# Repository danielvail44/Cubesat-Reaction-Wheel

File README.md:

# Cubesat-Reaction-Wheel
Low Cost Cubesat Reaction Wheel

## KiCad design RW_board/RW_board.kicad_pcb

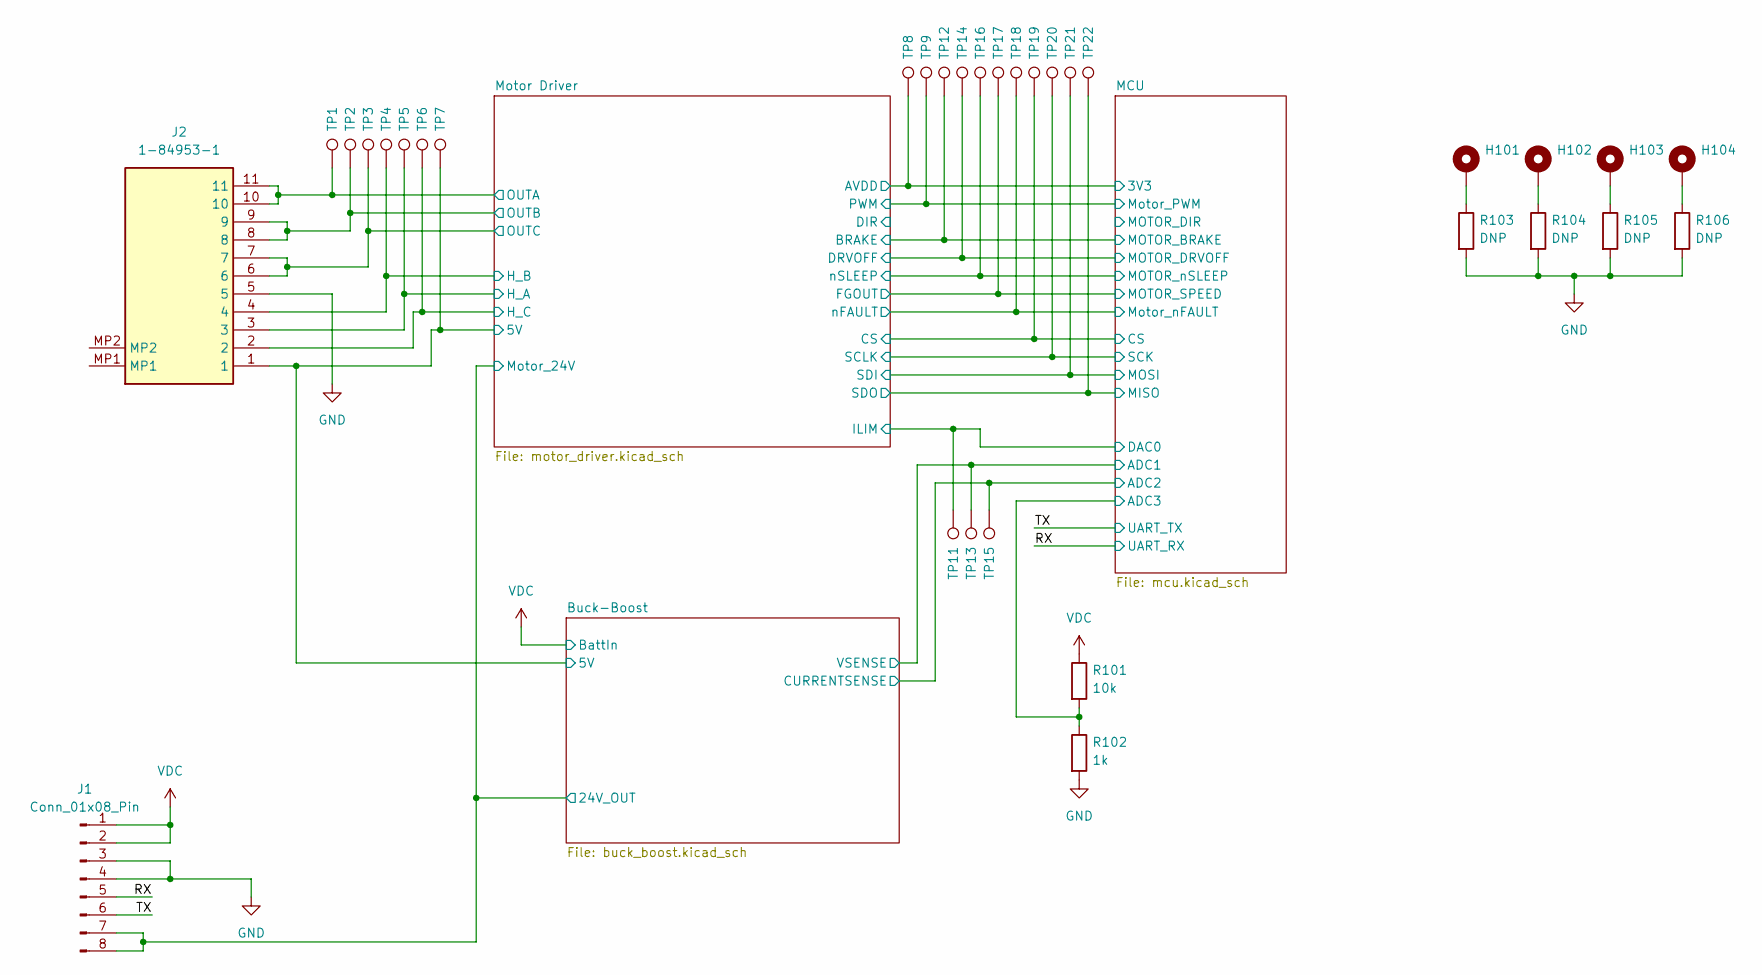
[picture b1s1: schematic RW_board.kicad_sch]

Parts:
H101, H102, H103, H104: MountingHole_Pad; MountingHole_3.4mm_Pad
J1: Conn_01x08_Pin; Molex_PicoBlade_53048-0810_1x08_P1.25mm_Horizontal; Mouser Part Number 538-53048-0810
J2: 1-84953-1; 1849531; Mouser Part Number 571-1-84953-1
R101: 10k; R_0402_1005Metric; Mouser Part Number 710-560112110020
R102: 1k; R_0402_1005Metric; Mouser Part Number 710-560112110012
R103, R104, R105, R106: DNP; R_0402_1005Metric
TP1, TP2, TP3, TP4, TP5, TP6, TP7, TP8, TP9, TP11, TP12, TP13, TP14, TP15, TP16, TP17, TP18, TP19, TP20, TP21, TP22: TestPoint; TestPoint_Pad_1.0x1.0mm

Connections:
+3.3V: TP8.1; also elsewhere on the board
/Buck-Boost/24V_OUT: J1.7, J1.8; also elsewhere on the board
/Buck-Boost/CURRENTSENSE: TP15.1; also elsewhere on the board
/Buck-Boost/VSENSE: TP13.1; also elsewhere on the board
/MCU/ADC3: R101.2, R102.1; also elsewhere on the board
/MCU/CS: TP19.1; also elsewhere on the board
/MCU/DAC0: TP11.1; also elsewhere on the board
/MCU/MISO: TP22.1; also elsewhere on the board
/MCU/MOSI: TP21.1; also elsewhere on the board
/MCU/MOTOR_BRAKE: TP12.1; also elsewhere on the board
/MCU/MOTOR_DRVOFF: TP14.1; also elsewhere on the board
/MCU/MOTOR_SPEED: TP17.1; also elsewhere on the board
/MCU/MOTOR_nSLEEP: TP16.1; also elsewhere on the board
/MCU/Motor_PWM: TP9.1; also elsewhere on the board
/MCU/Motor_nFAULT: TP18.1; also elsewhere on the board
/MCU/SCK: TP20.1; also elsewhere on the board
/Motor Driver/FB_BK: J2.1, TP7.1; also elsewhere on the board
/Motor Driver/H_A: J2.3, TP5.1; also elsewhere on the board
/Motor Driver/H_B: J2.4, TP4.1; also elsewhere on the board
/Motor Driver/H_C: J2.2, TP6.1; also elsewhere on the board
/Motor Driver/OUTA: J2.10, J2.11, TP1.1; also elsewhere on the board
/Motor Driver/OUTB: J2.8, J2.9, TP2.1; also elsewhere on the board
/Motor Driver/OUTC: J2.6, J2.7, TP3.1; also elsewhere on the board
/RX: J1.5; also elsewhere on the board
/TX: J1.6; also elsewhere on the board
GND: J1.3, J1.4, J2.5, R102.2, R103.2, R104.2, R105.2, R106.2; also elsewhere on the board
unnamed: H101.1, R103.1
unnamed: H102.1, R104.1
unnamed: H103.1, R105.1
unnamed: H104.1, R106.1
VDC: J1.1, J1.2, R101.1; also elsewhere on the board

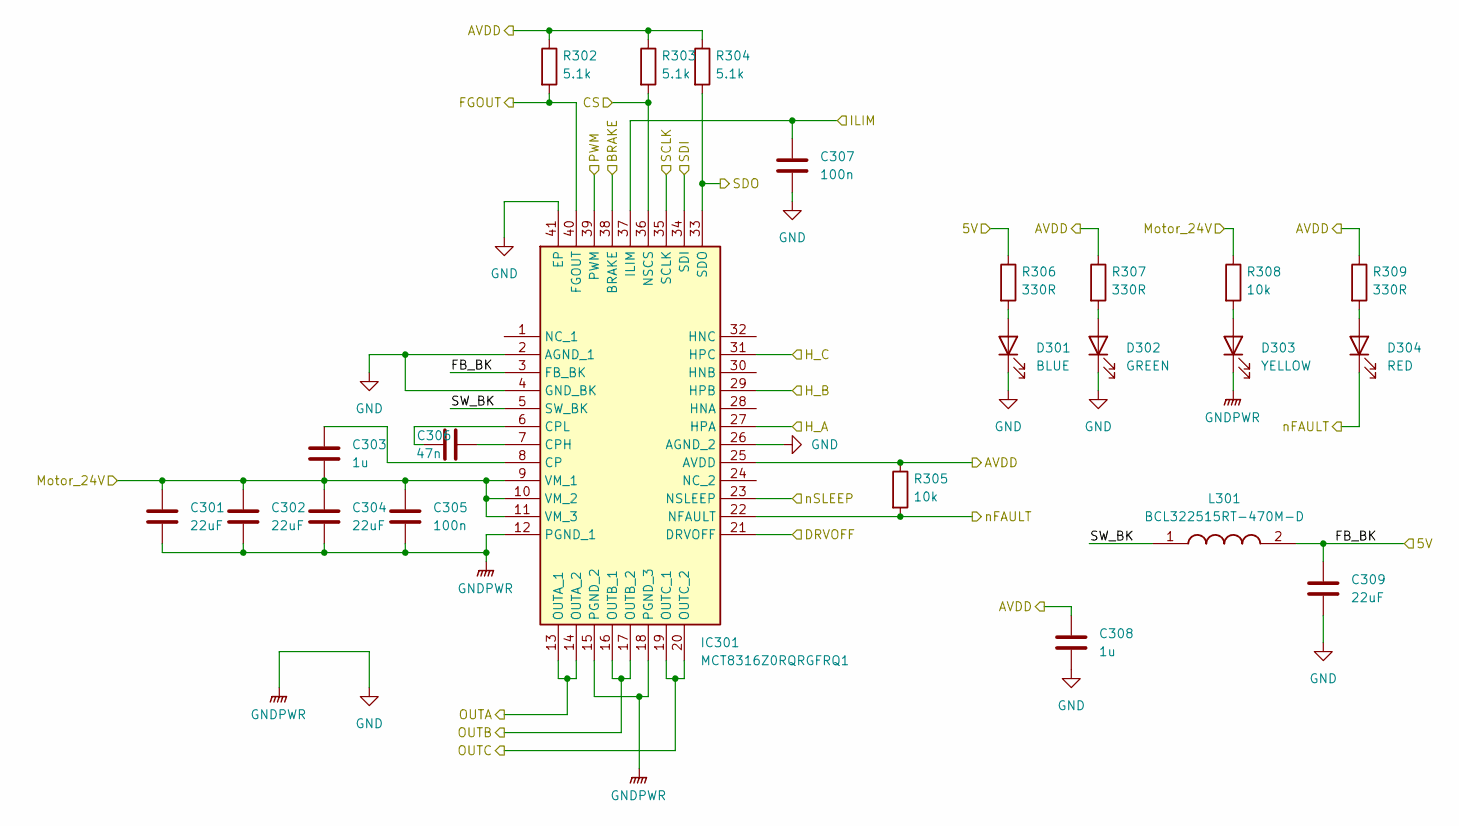
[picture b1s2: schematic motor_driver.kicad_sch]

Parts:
C301, C302, C304, C309: 22uF; C_0805_2012Metric; Voltage rating 35V; Mouser Part Number 810-C2012X5R1V226MAC
C303, C308: 1u; C_0402_1005Metric; Voltage rating 35V; Mouser Part Number 81-GRM155R6YA105KE1J
C305, C307: 100n; C_0402_1005Metric; Voltage rating 35V; Mouser Part Number 81-GRM155R61H104KE9J
C306: 47n; C_0402_1005Metric; Voltage rating 35V; Mouser Part Number 81-GRM155R61H473KE9D
D301: BLUE; LED_0603_1608Metric; Mouser Part Number 720-P4112P1R2363X4X5
D302: GREEN; LED_0603_1608Metric; Mouser Part Number 720-P4112S2U1252X4X5
D303: YELLOW; LED_0603_1608Metric; Mouser Part Number 720-P412Q2T136A8J802
D304: RED; LED_0603_1608Metric; Mouser Part Number 720-P412P1R258A8J802
IC301: MCT8316Z0RQRGFRQ1; QFN50P500X700X100-41N-D; Mouser Part Number 595-CT8316Z0RQRGFRQ1
L301: BCL322515RT-470M-D; INDPM3225X150N; Mouser Part Number 810-BCL322515RT470MD
R302, R303, R304: 5.1k; R_0402_1005Metric; Mouser Part Number 652-CR0402FX-5101GLF
R305, R308: 10k; R_0402_1005Metric; Mouser Part Number 710-560112110020
R306, R307, R309: 330R; R_0402_1005Metric; Mouser Part Number 710-560112110231

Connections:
+3.3V: C308.1, IC301.25 (AVDD), R302.1, R303.1, R304.1, R305.1, R307.1, R309.1; also elsewhere on the board
/Buck-Boost/24V_OUT: C301.1, C302.1, C303.2, C304.1, C305.1, IC301.9 (VM_1), IC301.10 (VM_2), IC301.11 (VM_3), R308.1; also elsewhere on the board
/MCU/CS: IC301.36 (NSCS), R303.2; also elsewhere on the board
/MCU/DAC0: C307.1, IC301.37 (ILIM); also elsewhere on the board
/MCU/MISO: IC301.33 (SDO), R304.2; also elsewhere on the board
/MCU/MOSI: IC301.34 (SDI); also elsewhere on the board
/MCU/MOTOR_BRAKE: IC301.38 (BRAKE); also elsewhere on the board
/MCU/MOTOR_DRVOFF: IC301.21 (DRVOFF); also elsewhere on the board
/MCU/MOTOR_SPEED: IC301.40 (FGOUT), R302.2; also elsewhere on the board
/MCU/MOTOR_nSLEEP: IC301.23 (NSLEEP); also elsewhere on the board
/MCU/Motor_PWM: IC301.39 (PWM); also elsewhere on the board
/MCU/Motor_nFAULT: D304.1 (K), IC301.22 (NFAULT), R305.2; also elsewhere on the board
/MCU/SCK: IC301.35 (SCLK); also elsewhere on the board
/Motor Driver/FB_BK: C309.1, IC301.3 (FB_BK), L301.2, R306.1; also elsewhere on the board
/Motor Driver/H_A: IC301.27 (HPA); also elsewhere on the board
/Motor Driver/H_B: IC301.29 (HPB); also elsewhere on the board
/Motor Driver/H_C: IC301.31 (HPC); also elsewhere on the board
/Motor Driver/OUTA: IC301.13 (OUTA_1), IC301.14 (OUTA_2); also elsewhere on the board
/Motor Driver/OUTB: IC301.16 (OUTB_1), IC301.17 (OUTB_2); also elsewhere on the board
/Motor Driver/OUTC: IC301.19 (OUTC_1), IC301.20 (OUTC_2); also elsewhere on the board
/Motor Driver/SW_BK: IC301.5 (SW_BK), L301.1
GND: C301.2, C302.2, C304.2, C305.2, C307.2, C308.2, C309.2, D301.1 (K), D302.1 (K), D303.1 (K), IC301.2 (AGND_1), IC301.4 (GND_BK), IC301.12 (PGND_1), IC301.15 (PGND_2), IC301.18 (PGND_3), IC301.26 (AGND_2), IC301.41 (EP); also elsewhere on the board
unnamed: D301.2 (A), R306.2
unnamed: D302.2 (A), R307.2
unnamed: D303.2 (A), R308.2
unnamed: D304.2 (A), R309.2
unnamed: C303.1, IC301.8 (CP)
unnamed: C306.2, IC301.7 (CPH)
unnamed: C306.1, IC301.6 (CPL)

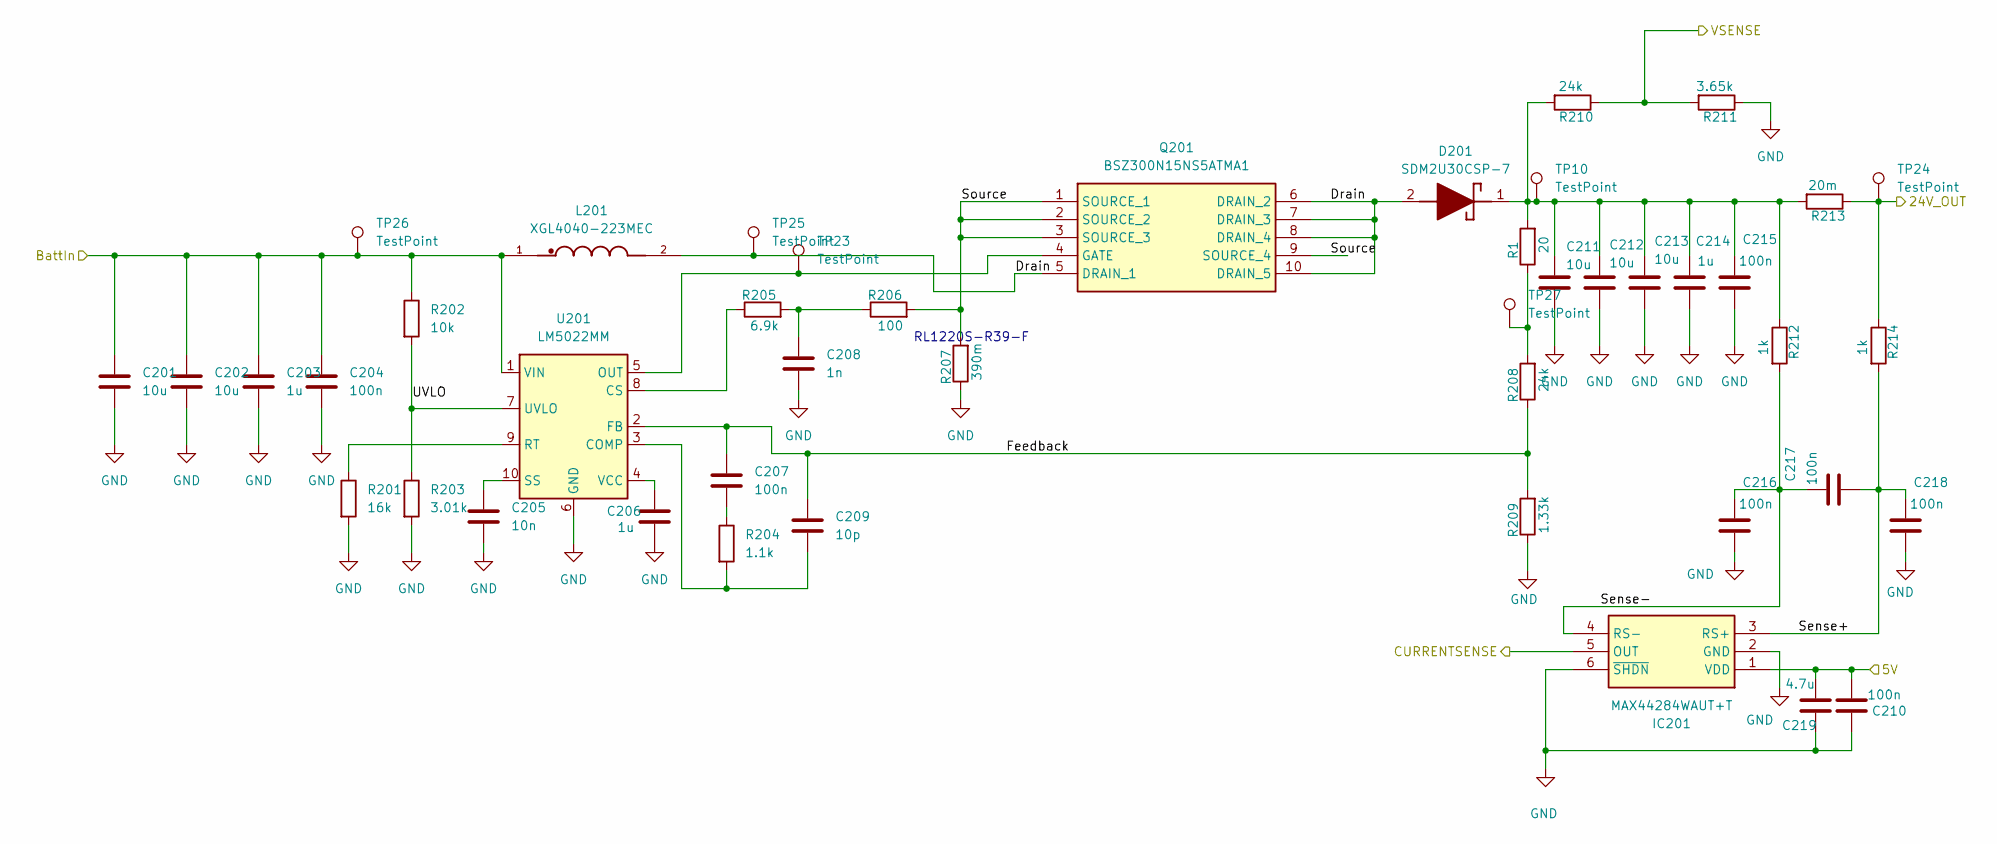
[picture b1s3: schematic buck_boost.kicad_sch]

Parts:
C201, C202, C211, C212, C213: 10u; C_0603_1608Metric; Voltage rating 35V; Mouser Part Number 81-GRM188R6YA106MA3D
C203, C206, C214: 1u; C_0402_1005Metric; Voltage rating 35V; Mouser Part Number 81-GRM155R6YA105KE1J
C204, C207, C210, C215, C216, C217, C218: 100n; C_0402_1005Metric; Voltage rating 35V; Mouser Part Number 81-GRM155R61H104KE9J
C205: 10n; C_0402_1005Metric; Voltage rating 35V; Mouser Part Number 81-GCM155R71H103KA5J
C208: 1n; C_0402_1005Metric; Voltage rating 35V; Mouser Part Number 81-GCM1555C1H102GA6J
C209: 10p; C_0402_1005Metric; Voltage rating 35V; Mouser Part Number 81-GCM1555C1H100JA6D
C219: 4.7u; C_0402_1005Metric; Voltage rating 35V; Mouser Part Number 81-GRM155R61A475MEAD
D201: SDM2U30CSP-7; X3-WLB1608-2; Mouser Part Number 621-SDM2U30CSP-7
IC201: MAX44284WAUT+T; SOT95P280X145-6N; Mouser Part Number 700-MAX44284WAUT+T
L201: XGL4040-223MEC; IND_XGL4040-223MEC; PARTREV 10/08/21
Q201: BSZ300N15NS5ATMA1; Mouser Part Number 726-BSZ300N15NS5ATMA
R1: 20; R_0402_1005Metric; Mouser Part Number 710-560112110083
R201: 16k; R_0402_1005Metric; Mouser Part Number 710-560112110032
R202: 10k; R_0402_1005Metric; Mouser Part Number 710-560112110020
R203: 3.01k; R_0402_1005Metric; Mouser Part Number 652-CRT0402FZ3011GLF
R204: 1.1k; R_0402_1005Metric; Mouser Part Number 710-560112110185
R205: 6.9k; R_0402_1005Metric; Mouser Part Number 603-RT0402BRD076K9L
R206: 100; R_0402_1005Metric; Mouser Part Number 710-560112110022
R207: 390m; R_0805_2012Metric; Manufacturer_Part_Number RL1220S-R39-F; Mouser Part Number 754-RL1220S-R39-F
R208, R210: 24k; R_0402_1005Metric; Mouser Part Number 710-560112110178
R209: 1.33k; R_0402_1005Metric; Mouser Part Number 652-CRT0402FZ1331GLF
R211: 3.65k; R_0402_1005Metric; Mouser Part Number 710-560112110116
R212, R214: 1k; R_0402_1005Metric; Mouser Part Number 710-560112110012
R213: 20m; R_0603_1608Metric; Mouser Part Number 603-PE0603DRF570R02L
TP10, TP23, TP24, TP25, TP26, TP27: TestPoint; TestPoint_Pad_1.0x1.0mm
U201: LM5022MM; MSOP-10_3x3mm_P0.5mm; Mouser Part Number 926-LM5022MMX/NOPB

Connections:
/Buck-Boost/24V_OUT: R213.1, R214.1, TP24.1; also elsewhere on the board
/Buck-Boost/CURRENTSENSE: IC201.5 (OUT); also elsewhere on the board
/Buck-Boost/Drain: D201.2 (A), L201.2, Q201.5 (DRAIN_1), Q201.6 (DRAIN_2), Q201.7 (DRAIN_3), Q201.8 (DRAIN_4), Q201.10 (DRAIN_5), TP25.1
/Buck-Boost/Feedback: C207.1, C209.1, R208.1, R209.2, U201.2 (FB)
/Buck-Boost/Sense+: C217.2, C218.1, IC201.3 (RS+), R214.2
/Buck-Boost/Sense-: C216.1, C217.1, IC201.4 (RS-), R212.2
/Buck-Boost/Source: Q201.1 (SOURCE_1), Q201.2 (SOURCE_2), Q201.3 (SOURCE_3), Q201.9 (SOURCE_4), R206.2, R207.2
/Buck-Boost/UVLO: R202.2, R203.1, U201.7 (UVLO)
/Buck-Boost/VSENSE: R210.1, R211.2; also elsewhere on the board
/Motor Driver/FB_BK: C210.2, C219.2, IC201.1 (VDD); also elsewhere on the board
GND: C201.2, C202.2, C203.2, C204.2, C205.2, C206.2, C208.2, C210.1, C211.2, C212.2, C213.2, C214.2, C215.2, C216.2, C218.2, C219.1, IC201.2 (GND), IC201.6 (~SHDN), R201.2, R203.2, R207.1, R209.1, R211.1, U201.6 (GND); also elsewhere on the board
unnamed: C207.2, R204.1
unnamed: C208.1, R205.2, R206.1
unnamed: C211.1, C212.1, C213.1, C214.1, C215.1, D201.1 (K), R1.2, R210.2, R212.1, R213.2, TP10.1
unnamed: Q201.4 (GATE), TP23.1, U201.5 (OUT)
unnamed: R1.1, R208.2, TP27.1
unnamed: C209.2, R204.2, U201.3 (COMP)
unnamed: R205.1, U201.8 (CS)
unnamed: R201.1, U201.9 (RT)
unnamed: C205.1, U201.10 (SS)
unnamed: C206.1, U201.4 (VCC)
VDC: C201.1, C202.1, C203.1, C204.1, L201.1, R202.1, TP26.1, U201.1 (VIN); also elsewhere on the board

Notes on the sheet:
RL1220S-R39-F

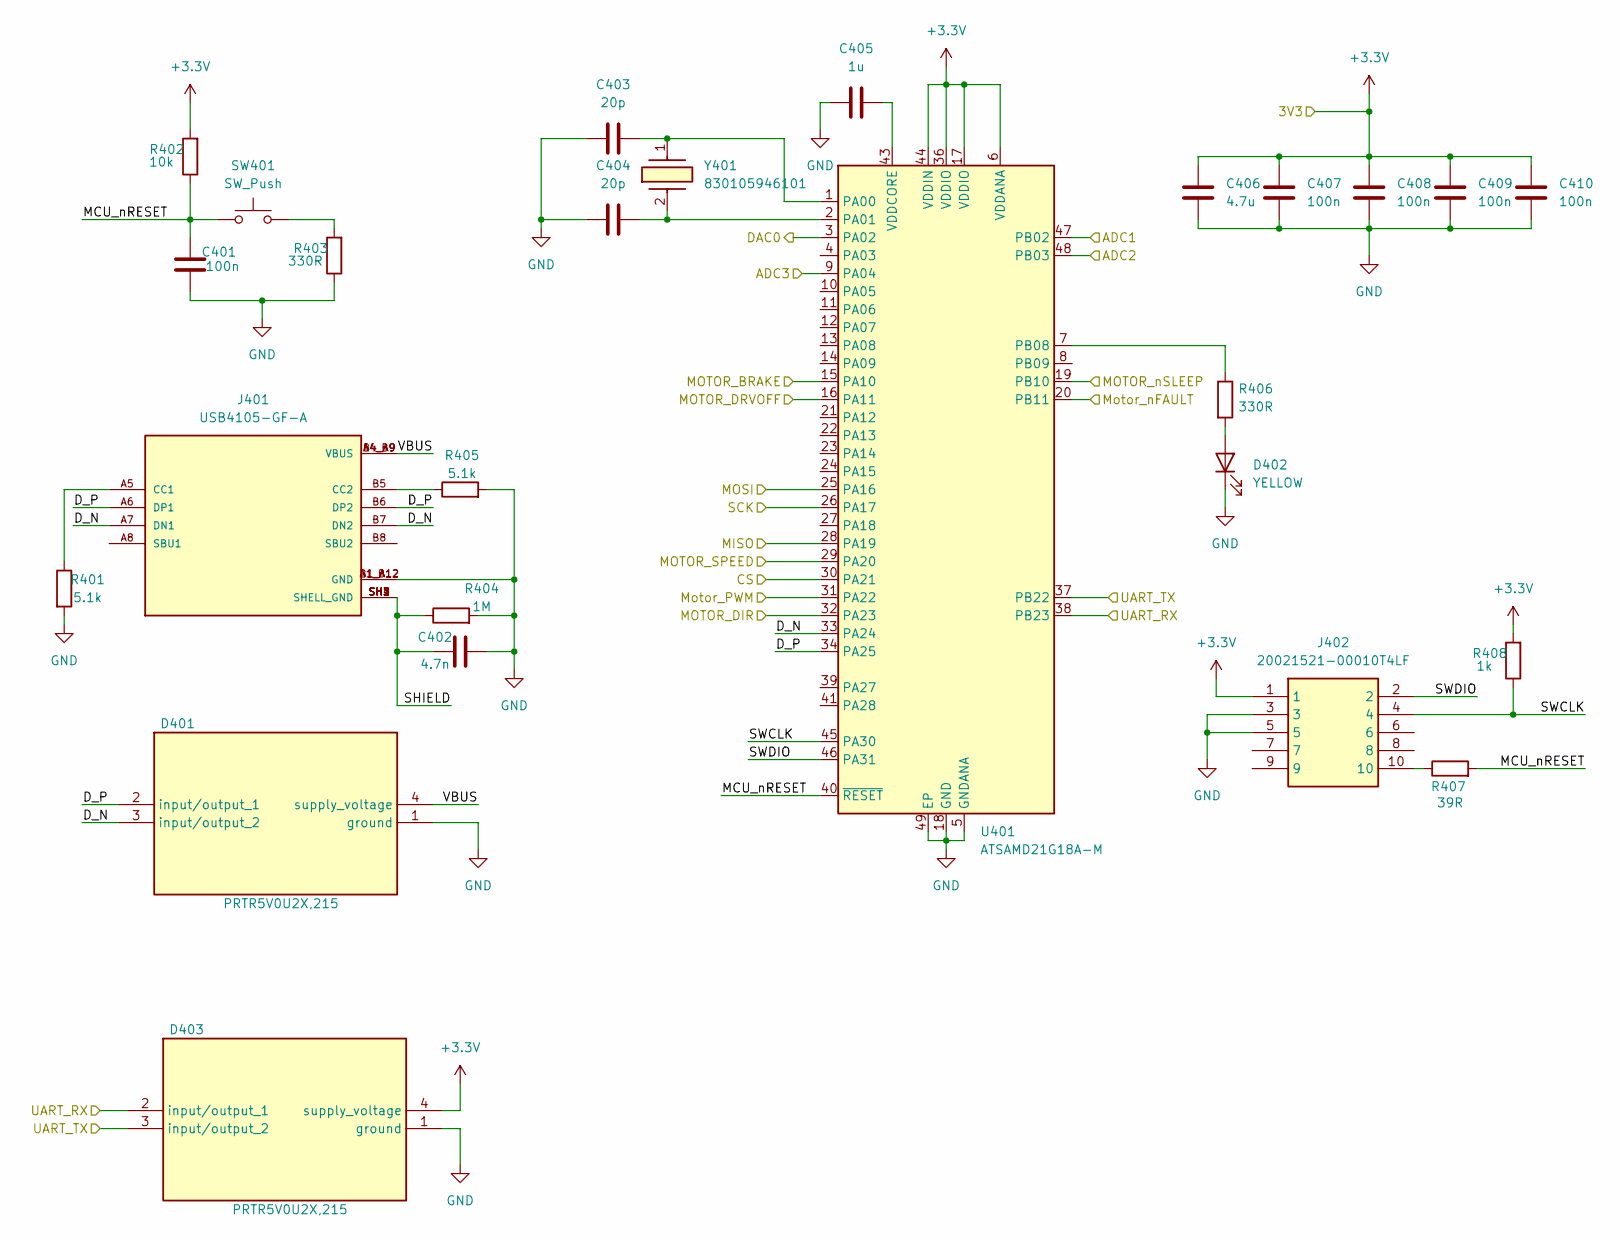
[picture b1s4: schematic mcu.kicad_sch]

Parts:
C401, C407, C408, C409, C410: 100n; C_0402_1005Metric; Voltage rating 35V; Mouser Part Number 81-GRM155R61H104KE9J
C402: 4.7n; C_0402_1005Metric; Voltage rating 35V; Mouser Part Number 81-GRM155R71H472JA1D
C403, C404: 20p; C_0402_1005Metric; Mouser Part Number 81-GRM1555C1H200JA1D
C405: 1u; C_0402_1005Metric; Voltage rating 35V; Mouser Part Number 81-GRM155R6YA105KE1J
C406: 4.7u; C_0402_1005Metric; Voltage rating 35V; Mouser Part Number 81-GRM155R61A475MEAD
D401, D403: PRTR5V0U2X,215; PRTR5V0U2X; Mouser Part Number 771-PRTR5V0U2X-T/R
D402: YELLOW; LED_0603_1608Metric; Mouser Part Number 720-P412Q2T136A8J802
J401: USB4105-GF-A; GCT_USB4105-GF-A; PARTREV B4; Mouser Part Number 640-USB4105-GF-A
J402: 20021521-00010T4LF; 2002152100010T4LF; Mouser Part Number 649-221521-00010T4LF
R401, R405: 5.1k; R_0402_1005Metric; Mouser Part Number 652-CR0402FX-5101GLF
R402: 10k; R_0402_1005Metric; Mouser Part Number 710-560112110020
R403, R406: 330R; R_0402_1005Metric; Mouser Part Number 710-560112110231
R404: 1M; R_0402_1005Metric; Mouser Part Number 710-560112110033
R407: 39R; R_0402_1005Metric; Mouser Part Number 710-560112110014
R408: 1k; R_0402_1005Metric; Mouser Part Number 710-560112110012
SW401: SW_Push; SW_SPST_FSMSM; Mouser Part Number 611-RS-282G05A3-SMRT
U401: ATSAMD21G18A-M; QFN-48-1EP_7x7mm_P0.5mm_EP5.15x5.15mm; Mouser Part Number 556-ATSAMD21G18A-MUT
Y401: 830105946101; Mouser Part Number 710-830105946101

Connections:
+3.3V: C406.2, C407.2, C408.2, C409.2, C410.2, D403.4 (supply_voltage), J402.1, R402.2, R408.2, U401.6 (VDDANA), U401.17 (VDDIO), U401.36 (VDDIO), U401.44 (VDDIN); also elsewhere on the board
/Buck-Boost/CURRENTSENSE: U401.48 (PB03); also elsewhere on the board
/Buck-Boost/VSENSE: U401.47 (PB02); also elsewhere on the board
/MCU/ADC3: U401.9 (PA04); also elsewhere on the board
/MCU/CS: U401.30 (PA21); also elsewhere on the board
/MCU/DAC0: U401.3 (PA02); also elsewhere on the board
/MCU/D_N: D401.3 (input/output_2), J401.A7 (DN1), J401.B7 (DN2), U401.33 (PA24)
/MCU/D_P: D401.2 (input/output_1), J401.A6 (DP1), J401.B6 (DP2), U401.34 (PA25)
/MCU/MCU_nRESET: C401.2, R402.1, R407.2, SW401.1, U401.40 (~RESET)
/MCU/MISO: U401.28 (PA19); also elsewhere on the board
/MCU/MOSI: U401.25 (PA16); also elsewhere on the board
/MCU/MOTOR_BRAKE: U401.15 (PA10); also elsewhere on the board
/MCU/MOTOR_DIR: U401.32 (PA23)
/MCU/MOTOR_DRVOFF: U401.16 (PA11); also elsewhere on the board
/MCU/MOTOR_SPEED: U401.29 (PA20); also elsewhere on the board
/MCU/MOTOR_nSLEEP: U401.19 (PB10); also elsewhere on the board
/MCU/Motor_PWM: U401.31 (PA22); also elsewhere on the board
/MCU/Motor_nFAULT: U401.20 (PB11); also elsewhere on the board
/MCU/SCK: U401.26 (PA17); also elsewhere on the board
/MCU/SHIELD: C402.1, J401.SH1 (SHELL_GND), J401.SH2 (SHELL_GND), J401.SH3 (SHELL_GND), J401.SH4 (SHELL_GND), R404.1
/MCU/SWCLK: J402.4, R408.1, U401.45 (PA30)
/MCU/SWDIO: J402.2, U401.46 (PA31)
/MCU/VBUS: D401.4 (supply_voltage), J401.A4_B9 (VBUS), J401.B4_A9 (VBUS)
/RX: D403.2 (input/output_1), U401.38 (PB23); also elsewhere on the board
/TX: D403.3 (input/output_2), U401.37 (PB22); also elsewhere on the board
GND: C401.1, C402.2, C403.1, C404.1, C405.1, C406.1, C407.1, C408.1, C409.1, C410.1, D401.1 (ground), D402.1 (K), D403.1 (ground), J401.A1_B12 (GND), J401.B1_A12 (GND), J402.3, J402.5, R401.2, R403.1, R404.2, R405.2, U401.5 (GNDANA), U401.18 (GND), U401.35 (GND), U401.42 (GND), U401.49 (EP); also elsewhere on the board
unnamed: D402.2 (A), R406.2
unnamed: J401.A5 (CC1), R401.1
unnamed: J401.B5 (CC2), R405.1
unnamed: J402.10, R407.1
unnamed: R403.2, SW401.2
unnamed: C403.2, U401.1 (PA00), Y401.1
unnamed: C404.2, U401.2 (PA01), Y401.2 (CRYSTAL_2)
unnamed: R406.1, U401.7 (PB08)
unnamed: C405.2, U401.43 (VDDCORE)

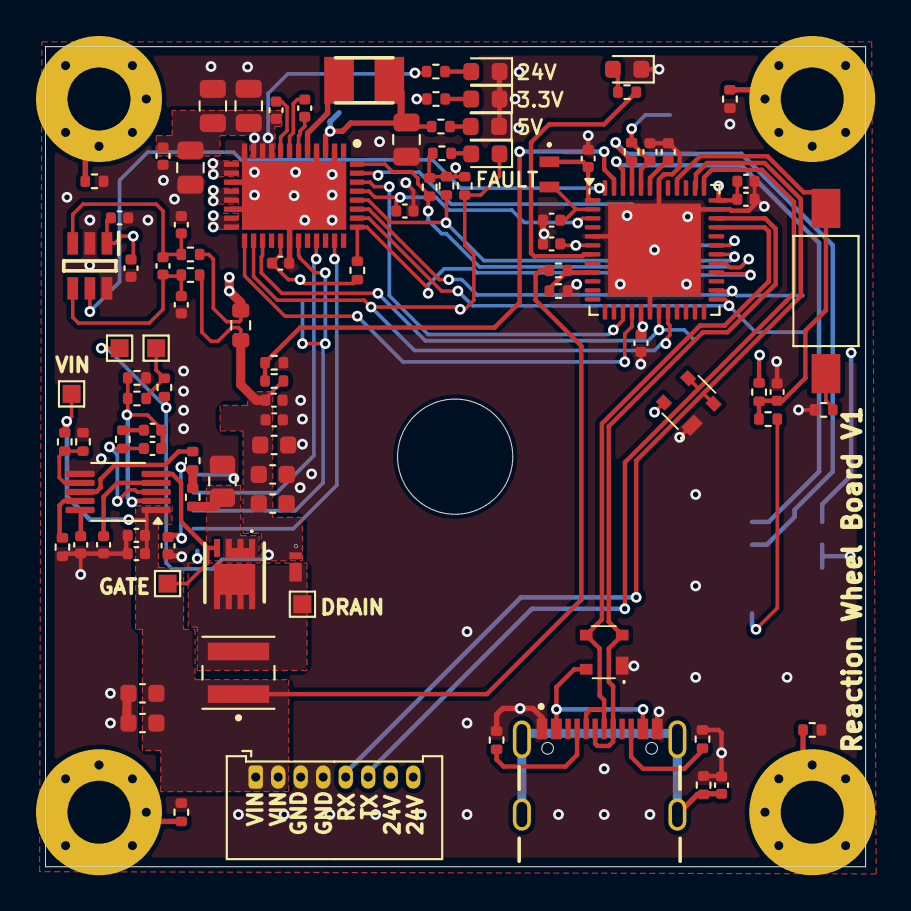
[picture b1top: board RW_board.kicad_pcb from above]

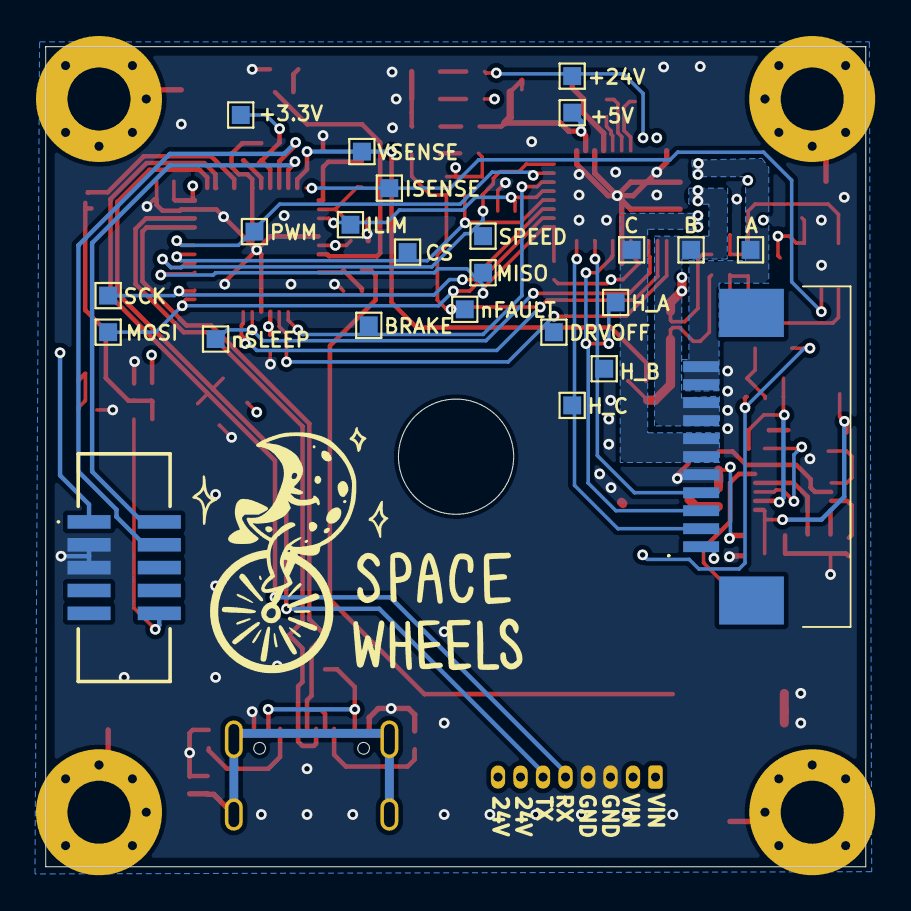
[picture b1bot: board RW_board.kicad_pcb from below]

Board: 4 copper layers, 45.6 x 45.6 mm, 127 parts (24 on the bottom side), 71 nets.

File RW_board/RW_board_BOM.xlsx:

Reference | Value | Datasheet | Footprint | Qty | Order Qty | Manufacturer_Part_Number | Mouser Part Number | Voltage rating | DKPN | Alt Link |  | Cart Links
C201,C202,C211,C212,C213 | 10u | ~ | Capacitor_SMD:C_0603_1608Metric | 5 | 15 | GRM188R6YA106MA73D | 81-GRM188R6YA106MA3D | 35V | 490-13248-1-ND | . |  | https://www.mouser.com/ProjectManager/ProjectDetail.aspx?Acc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
C203,C206,C214,C303,C308,C405 | 1u | ~ | Capacitor_SMD:C_0402_1005Metric | 6 | 18 | GRM155R6YA105KE11J | 81-GRM155R6YA105KE1J | 35V | 490-GRM155R6YA105KE11JCT-ND | . |  | https://www.digikey.com/short/zz49hznb
C204,C207,C210,C215,C216,C217,C218,C305,C307,C401,C407,C408,C409,C410 | 100n | ~ | Capacitor_SMD:C_0402_1005Metric | 14 | 42 | GRM155R61H104KE19J | 81-GRM155R61H104KE9J | 35V | 490-GRM155R61H104KE19JCT-ND | .
C205 | 10n | ~ | Capacitor_SMD:C_0402_1005Metric | 1 | 10 | GCM155R71H103KA55J | 81-GCM155R71H103KA5J | 35V | 490-13295-1-ND | .
C208 | 1n | ~ | Capacitor_SMD:C_0402_1005Metric | 1 | 10 | GCM1555C1H102GA16J | 81-GCM1555C1H102GA6J | 35V | 490-GCM1555C1H102GA16JCT-ND | .
C209 | 10p | ~ | Capacitor_SMD:C_0402_1005Metric | 1 | 10 | GCM1555C1H100JA16D | 81-GCM1555C1H100JA6D | 35V | 490-10668-1-ND | .
C219,C406 | 4.7u | ~ | Capacitor_SMD:C_0402_1005Metric | 2 | 10 | GRM155R61A475MEAAD | 81-GRM155R61A475MEAD | 35V | 490-14306-1-ND | .
C301,C302,C304,C309 | 22uF | ~ | Capacitor_SMD:C_0805_2012Metric | 4 | 12 | C2012X5R1V226M125AC | 810-C2012X5R1V226MAC | 35V | 445-14428-1-ND | .
C306 | 47n | ~ | Capacitor_SMD:C_0402_1005Metric | 1 | 10 | GRM155R61H473KE19D | 81-GRM155R61H473KE9D | 35V | 490-12705-1-ND | .
C402 | 4.7n | ~ | Capacitor_SMD:C_0402_1005Metric | 1 | 10 | GRM155R71H472JA01D | 81-GRM155R71H472JA1D | 35V | 490-7764-1-ND | .
C403,C404 | 20p | ~ | Capacitor_SMD:C_0402_1005Metric | 2 | 10 | GRM1555C1H200JA01D | 81-GRM1555C1H200JA1D |  | 490-5930-1-ND | .
D201 | SDM2U30CSP-7 | https://www.diodes.com//assets/Datasheets/SDM2U30CSP.pdf | X3-WLB1608-2 | 1 | 2 | SDM2U30CSP-7 | 621-SDM2U30CSP-7 |  | SDM2U30CSP-7DICT-ND | .
D301 | BLUE | ~ | LED_SMD:LED_0603_1608Metric | 1 | 3 | 475-KBEELP41.12-P1R2-36-3X4X-5-R18CT-ND | 720-P4112P1R2363X4X5 |  | 475-KBEELP41.12-P1R2-36-3X4X-5-R18CT-ND | .
D302 | GREEN | ~ | LED_SMD:LED_0603_1608Metric | 1 | 3 | KT EELP41.12-S2U1-25-2X4X-5-R18 | 720-P4112S2U1252X4X5 |  | 475-KTEELP41.12-S2U1-25-2X4X-5-R18CT-ND | .
D303,D402 | YELLOW | ~ | LED_SMD:LED_0603_1608Metric | 2 | 3 | KY EELP41.22 Q2T1-36-A8J8-020-R18 | 720-P412Q2T136A8J802 |  | 475-KYEELP41.22Q2T1-36-A8J8-020-R18CT-ND | .
D304 | RED | ~ | LED_SMD:LED_0603_1608Metric | 1 | 3 | KS EELP41.22-P1R2-58-A8J8-020-R18 | 720-P412P1R258A8J802 |  | 475-KSEELP41.22-P1R2-58-A8J8-020-R18CT-ND | .
D401,D403 | PRTR5V0U2X,215 | https://assets.nexperia.com/documents/data-sheet/PRTR5V0U2X.pdf | PRTR5V0U2X | 2 | 4 | PRTR5V0U2X,215 | 771-PRTR5V0U2X-T/R |  | 1727-3884-1-ND | .
IC201 | MAX44284WAUT+T | https://datasheets.maximintegrated.com/en/ds/MAX44284.pdf | SOT95P280X145-6N | 1 | 2 | MAX44284WAUT+T | 700-MAX44284WAUT+T |  | 175-MAX44284WAUT+TCT-ND | .
IC301 | MCT8316Z0RQRGFRQ1 | https://www.ti.com/lit/ds/symlink/mct8316z-q1.pdf?ts=1673673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 | QFN50P500X700X100-41N-D | 1 | 2 | MCT8316Z0RQRGFRQ1 | 595-CT8316Z0RQRGFRQ1 |  | 296-MCT8316Z0RQRGFRQ1CT-ND | .
J1 | Conn_01x08_Pin | ~ | Connector_Molex:Molex_PicoBlade_53048-0810_1x08_P1.25mm_Horizontal | 1 | 2 | 53048-0810 | 538-53048-0810 |  | WM1748-ND | .
J2 | 1-84953-1 | https://www.te.com/commerce/DocumentDelivery/DDEController?A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 | 1849531 | 1 | 2 | 1-84953-1 | 571-1-84953-1 |  | A101403CT-ND | .
J401 | USB4105-GF-A |  | RW_Imports:GCT_USB4105-GF-A | 1 | 2 | USB4105-GF-A | 640-USB4105-GF-A |  | 2073-USB4105-GF-ACT-ND | .
J402 | 20021521-00010T4LF | https://cdn.amphenol-cs.com/media/wysiwyg/files/drawing/2002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 | 2002152100010T4LF | 1 | 2 | 20021521-00010T4LF | 649-221521-00010T4LF |  | 609-6534-ND | .
L301 | BCL322515RT-470M-D | https://product.tdk.com/system/files/dam/doc/product/inducto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 | RW_Imports:INDPM3225X150N | 1 | 2 | BCL322515RT-470M-D | 810-BCL322515RT470MD |  | 445-BCL322515RT-470M-DCT-ND | .
R1 | 20 | ~ | Resistor_SMD:R_0402_1005Metric | 1 | 10 | 560112110083 | 710-560112110083 |  | 732-560112110083CT-ND | .
R101,R202,R305,R308,R402 | 10k | ~ | Resistor_SMD:R_0402_1005Metric | 5 | 15 | 560112110020 | 710-560112110020 |  | 732-560112110020CT-ND | .
R102,R212,R214,R408 | 1k | ~ | Resistor_SMD:R_0402_1005Metric | 4 | 12 | 560112110012 | 710-560112110012 |  | 732-560112110012CT-ND | .
R201 | 16k | ~ | Resistor_SMD:R_0402_1005Metric | 1 | 10 | 560112110032 | 710-560112110032 |  | 732-560112110032CT-ND | .
R203 | 3.01k | ~ | Resistor_SMD:R_0402_1005Metric | 1 | 10 | CRT0402-FZ-3011GLF | 652-CRT0402FZ3011GLF |  | 311-3.01KLRCT-ND | .
R204 | 1.1k | ~ | Resistor_SMD:R_0402_1005Metric | 1 | 10 | 560112110185 | 710-560112110185 |  | 732-560112110185CT-ND | .
R205 | 6.9k | ~ | Resistor_SMD:R_0402_1005Metric | 1 | 10 | RT0402BRD076K9L | 71-TNPW04026K90BEED |  | 541-4510-1-ND | .
R206 | 100 | ~ | Resistor_SMD:R_0402_1005Metric | 1 | 10 | 560112110022 | 710-560112110022 |  | 732-560112110022CT-ND | .
R207 | 390m | ~ | Resistor_SMD:R_0805_2012Metric | 1 | 10 | RL1220S-R39-F | 754-RL1220S-R39-F |  | RL12S.39FCT-ND | .
R208,R210 | 24k | ~ | Resistor_SMD:R_0402_1005Metric | 2 | 10 | 560112110178 | 710-560112110178 |  | 311-24KJRCT-ND | .
R209 | 1.33k | ~ | Resistor_SMD:R_0402_1005Metric | 1 | 10 | CRT0402-FZ-1331GLF | 652-CRT0402FZ1331GLF |  | 311-1.33KLRCT-ND | .
R211 | 3.65k | ~ | Resistor_SMD:R_0402_1005Metric | 1 | 10 | 560112110116 | 710-560112110116 |  | 732-560112110116CT-ND | .
R213 | 20m | ~ | Resistor_SMD:R_0603_1608Metric | 1 | 10 | PE0603DRF570R02L | 603-PE0603DRF570R02L |  | 13-PE0603DRF570R02LCT-ND | .
R302,R303,R304,R401,R405 | 5.1k | ~ | Resistor_SMD:R_0402_1005Metric | 5 | 15 | CR0402-FX-5101GLF | 652-CR0402FX-5101GLF |  | CR0402-FX-5101GLFCT-ND | .
R306,R307,R309,R403,R406 | 330R | ~ | Resistor_SMD:R_0402_1005Metric | 5 | 15 | 560112110231 | 710-560112110231 |  | 732-560112110231CT-ND | .
R404 | 1M | ~ | Resistor_SMD:R_0402_1005Metric | 1 | 10 | 560112110033 | 710-560112110033 |  | 732-560112110033CT-ND | .
R407 | 39R | ~ | Resistor_SMD:R_0402_1005Metric | 1 | 10 | 560112110014 | 710-560112110014 |  | 732-560112110014CT-ND | .
SW401 | SW_Push | ~ | Button_Switch_SMD:SW_SPST_FSMSM | 1 | 2 | RS282G05A3SMRT | 611-RS-282G05A3-SMRT |  | CKN10384CT-ND | .
U201 | LM5022MM | http://www.ti.com/lit/ds/symlink/lm5022.pdf | Package_SO:MSOP-10_3x3mm_P0.5mm | 1 | 2 | LM5022MMX/NOPB | 926-LM5022MMX/NOPB |  | 296-LM5022MMX/NOPBCT-ND | .
U401 | ATSAMD21G18A-M | http://ww1.microchip.com/downloads/en/DeviceDoc/SAM_D21_DA1_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 | Package_DFN_QFN:QFN-48-1EP_7x7mm_P0.5mm_EP5.15x5.15mm | 1 | 2 | ATSAMD21G18A-MUT | 556-ATSAMD21G18A-MUT |  | ATSAMD21G18A-MUTCT-ND | .
Y401 | 830105946101 | https://www.mouser.tw/datasheet/2/445/830105946101-2005497.pdf | 830105946101 | 1 | 2 | 830105946101 | 710-830105946101 |  | 1923-830105946101CT-ND | .
L201 | XGL4040-223MEC |  | RW_Imports:IND_XGL4040-223MEC | 1 | 2 | XGL4040-223 |  |  | 2457-XGL4040-223MEC-ND | https://www.coilcraft.com/en-us/products/power/shielded-indu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
Q201 | BSZ300N15NS5ATMA1 | https://www.arrow.com/en/products/bsz300n15ns5atma1/infineon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 | BSZ300N15NS5ATMA1 | 1 | 2 | BSZ300N15NS5ATMA1 |  |  | BSZ300N15NS5ATMA1CT-ND | https://www.rocelec.com/part/01tRl000007YmmJIAS-NCP1117DT12RKG

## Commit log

2025-01-08 Started working on motor driver schematic, added libraries, added motor cad
2025-01-08 Added motor symbol/footprint, worked more on schematic
2025-01-10 Switched to MCT8316, added supporting components
2025-01-13 Completed motor driver schematic
2025-01-13 Revert "Completed motor driver schematic"
    This reverts commit 6eff020a4600c20233f645a88c0bbf96158f60b4.
2025-01-13 Completed MCU schematic, connected with driver schematic
2025-01-20 Switched motor, added connectors, finished up design
2025-01-21 Implemented Initial Schematic of Boost Converter
    Some part values not fully defined but expected footprint added
2025-01-21 Picoblade footprint
2025-01-22 Fixed reset switch
2025-01-22 Fixed text
2025-01-22 Boost Converter Update: V & C Sense
    Added voltage and current sensing
2025-01-22 Added ADC inputs
2025-01-24 Connected everything, added testpoints
2025-01-24 Initial board layout
2025-01-24 Fixed some Boost sillyness
    Added Testpoints, another cap for Curr sense IC, and fixed mosfet pinout
2025-01-24 Some more boost changes
2025-01-25 Initial routing complete
2025-01-29 Board complete
2025-01-29 Added logo, TVS diode, made test production files
2025-01-29 via fix
2025-01-30 Update mounting holes
2025-02-03 Boost Testpoint Update
    2 Testpoints added to schematic and layout
2025-02-04 Curr Sense Edits & 24V Reroute
2025-02-04 Changed Footprints
    Hand Solder to not
2025-02-04 Add part numbers
2025-02-05 Bom completed and generated, minor PCB adjustments
2025-02-05 BOM excel added
2025-02-05 fix silkscreen
2025-02-05 Updated logo silkscreen, generated production files
2025-02-06 PCBWay production files
